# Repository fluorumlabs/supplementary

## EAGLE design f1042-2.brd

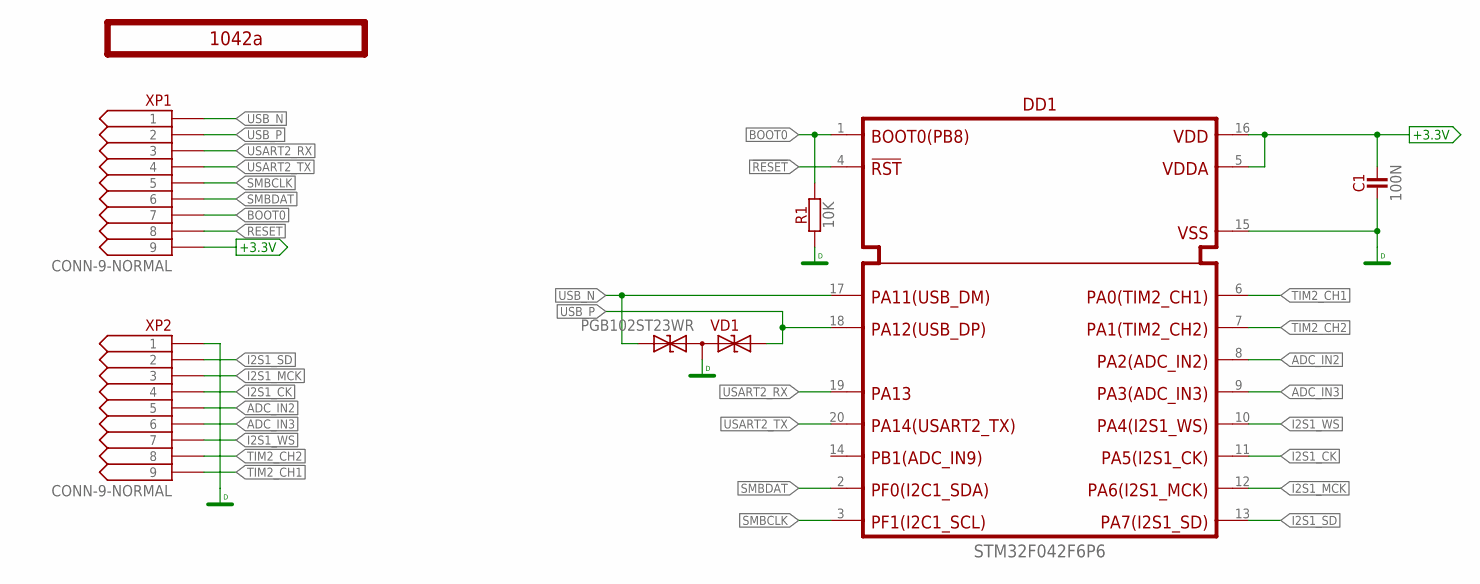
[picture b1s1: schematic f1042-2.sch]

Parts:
C1: 100N; C-0805
DD1: STM32F042F6P6; TSSOP20
PCB1: 1042a; F-LOGO
R1: 10K; R-0805
VD1: PGB102ST23WR; SOT23
XP1, XP2: CONN-9-NORMAL; MA03-9

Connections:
!RESET: DD1.4 (!RST), XP1.8
+3.3V: C1.2, DD1.5 (VDDA), DD1.16 (VDD), XP1.9
ADC_IN2: DD1.8 (PA2), XP2.5
ADC_IN3: DD1.9 (PA3), XP2.6
BOOT0: DD1.1 (BOOT0), R1.2, XP1.7
DGND: C1.1, DD1.15 (VSS), R1.1, VD1.3 (C), XP2.1
I2S1_CK: DD1.11 (PA5), XP2.4
I2S1_MCK: DD1.12 (PA6), XP2.3
I2S1_SD: DD1.13 (PA7), XP2.2
I2S1_WS: DD1.10 (PA4), XP2.7
SMBCLK: DD1.3 (PF1), XP1.5
SMBDAT: DD1.2 (PF0), XP1.6
TIM2_CH1: DD1.6 (PA0), XP2.9
TIM2_CH2: DD1.7 (PA1), XP2.8
USART2_RX: DD1.19 (PA13), XP1.3
USART2_TX: DD1.20 (PA14), XP1.4
USB_N: DD1.17 (PA11), VD1.2 (A1), XP1.1
USB_P: DD1.18 (PA12), VD1.1 (A), XP1.2

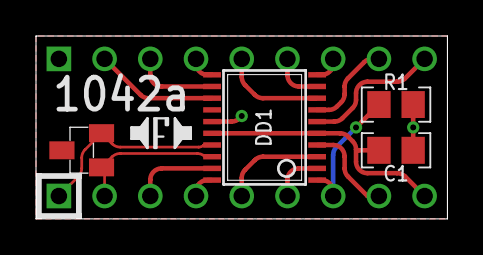
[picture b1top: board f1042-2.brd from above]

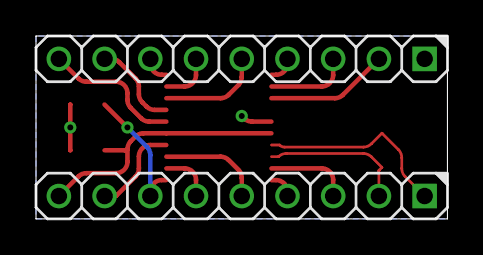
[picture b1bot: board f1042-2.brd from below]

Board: 2 copper layers, 22.9 x 10.2 mm, 7 parts (2 on the bottom side), 18 nets.

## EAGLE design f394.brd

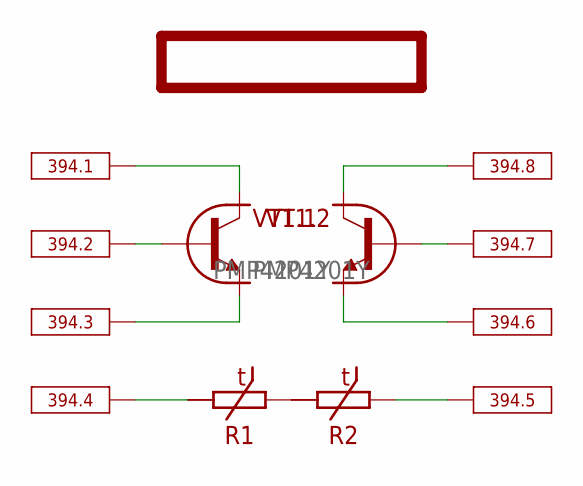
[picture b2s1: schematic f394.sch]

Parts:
394: DIP8; BA3760X8
R1, R2: ERA-V33J102V; R-0603
VT1: PMP4201Y; SOT363_PHILIPS

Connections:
B1: 394.B2, 394.T2, VT1.1 (B)
B2: 394.B7, 394.T7, VT1.2 (B)
unnamed: 394.B1, 394.T1, VT1.6 (C)
unnamed: 394.B6, 394.T6, VT1.4 (E)
unnamed: 394.B8, 394.T8, VT1.3 (C)
unnamed: 394.B3, 394.T3, VT1.5 (E)
unnamed: R1.2 (E), R2.1 (A)
unnamed: 394.B4, 394.T4, R1.1 (A)
unnamed: 394.B5, 394.T5, R2.2 (E)

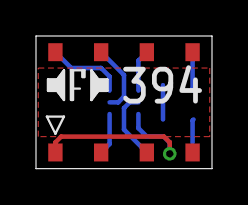
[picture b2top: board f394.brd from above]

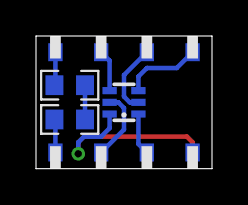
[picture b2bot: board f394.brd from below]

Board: 2 copper layers, 9.8 x 7.4 mm, 4 parts (3 on the bottom side), 9 nets.

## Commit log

2015-11-20 Initial F394 commit
2016-03-21 Initial F1042 commit
2016-03-21 F1042 Silkscreen fix
2016-04-01 Update F394 to use PMP4201Y
2016-04-01 Change PTC positioning
2016-04-01 F394 Routing Update
2016-06-01 Add F1042-2 without connector
2020-12-02 Add .whitesource configuration file
